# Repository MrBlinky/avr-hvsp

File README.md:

# avr-hvsp
High voltage serial programmer for AVR Attiny devices

* Easy to make programmer using 12V DC-DC converter with enable and ATMEGA32U4 Beetle board.
* Programs AVR Attiny devices in high voltage mode to recover fuse settings and allow reset pin to be used as GPIO pin.
* Works with Arduino IDE / AVRdude.
* No hassle with Windows driver utilities. Uses built in windows 10 driver or Arduino IDE driver.

## Parts

|Qty. | Discription                                                    |
| --- | -------------------------------------------------------------- |
| 1   | 12V DC-DC converter/booster module with enable                 |
| 1   | ATMEGA32U4 Beetle board without parts on PCB bottom + headers (No 3.3V pin and no extra GND pins on top row.) |
| 1   | 3 mm Red LED                                                   |
| 1   | 3 mm Yellow LED                                                |
| 1   | 3 mm Green LED                                                 |
| 5   | 470 Ohm resistor  (1/8 Watt)                                   |
| 2   | 1K resistor (1/8 Watt)                                         |
| 1   | PM48XP P-channel MOSFET SOT23 package (optional)*              |
| 1   | 8 pin header (for programming connector)                       |
| 1   | 2 pin header (for DC-DC converter)                             |
| 3   | 1 pin header (for DC-DC converter)                             |
| 1   | 8 pin IC socket                                                |
| 1   | 6x6mm tactile button                                           |
 
*A MOSFET is recommended for a more powerful VCC. However if devices are
 only programmed using the IC socket or in low power circuits (<20mA),
 the MOSFET can be left out. In that case VCC is powered by a GPIO pin
 by shorting jumper J1. When using a MOSFET, Jumper J1 must be left open.

Revision 1.1 PCB can be ordered through [OSH Park](https://oshpark.com/shared_projects/vXxMrB8z)

## Assembly

Assemble parts with low height first (programming header, MOSFET at bottom, resistors IC socket, button, LEDs and modules as last).
Check a parts aligment after soldering the first pin and when it's aligned properly solder remaining pins.

Before soldering the module headers, place headers with long end into main PCB and mount modules on top for easy aligment. Solder one pin of each header at top of module and check if headers are straight then solder remaining pins at top of the modules. Cut excess length of header pins at bottom of the main PCB and then solder them.

## upload programmer firmware

* Open **hvsp.ino** sketch by double clicking or open file with Arduino IDE
* Select **Arduino Leonardo** board from **Tools** menu.
* Select **port** from **Tools** menu.
* Upload sketch

## Programming a device

Insert 8-pin DIP devices in to socket or wire-up device to programming header (check device datasheet for wiring).
Upload a sketch using Arduino IDE or upload a hex file directly using AVRdude.

LED status:
* Red LED on: 12V VPP programming voltage on. Red LED off: Programming voltage off.
* Yellow LED on: 5V VCC on. Yellow LED off: 5V VCC off.
* Green LED on: Both programming and VCC are off. Green LED off: VPP and/or VCC on.

Button control:

Short press (< 500 ms): Toggle VCC on/off.
long press (>= 500 ms): TO DO

### using Arduino IDE

select **Arduino as ISP (ATmega32U4)** as **programmer** from **Tools** menu

### using AVRdude

Use **-carduino** as programmer switch and specify serial port with *-P* switch

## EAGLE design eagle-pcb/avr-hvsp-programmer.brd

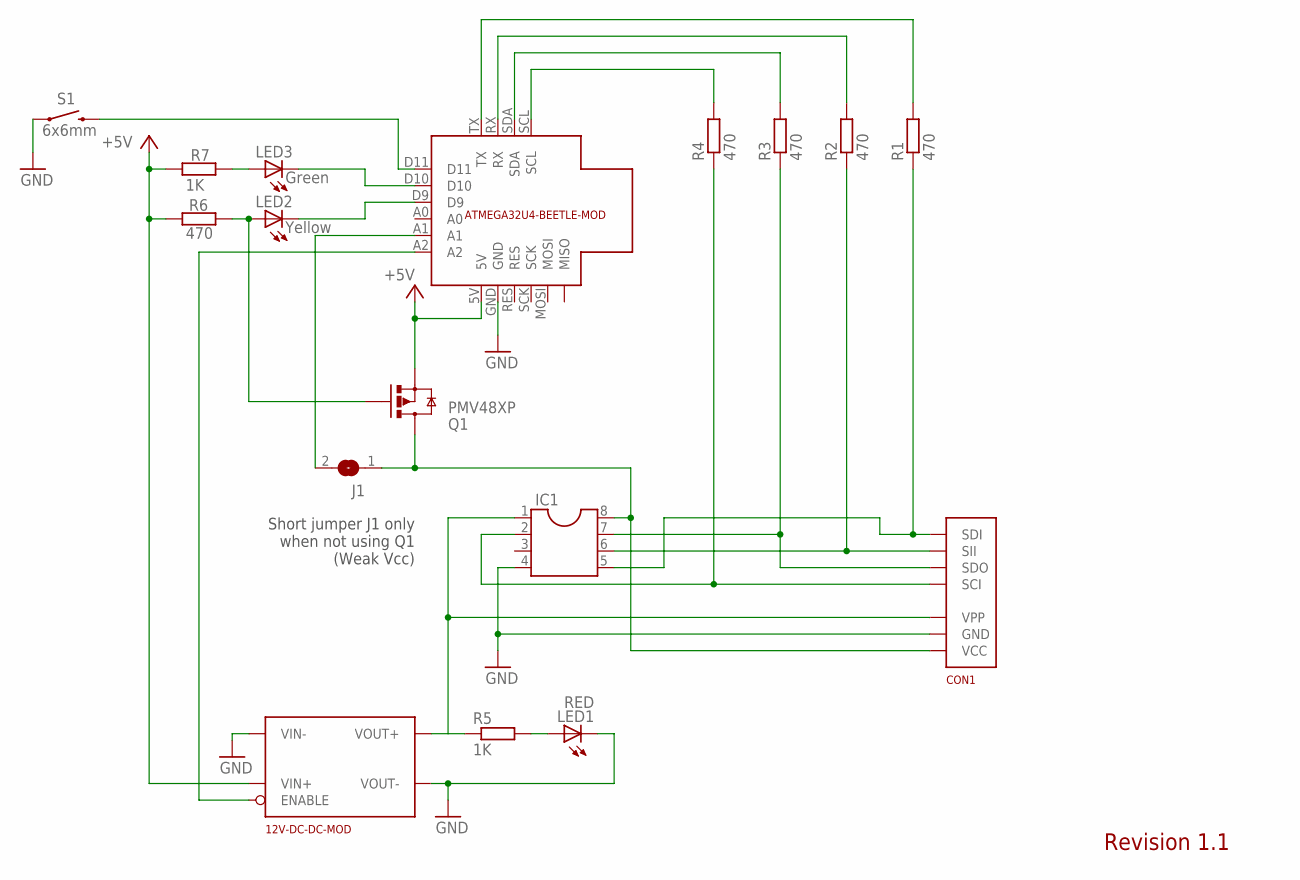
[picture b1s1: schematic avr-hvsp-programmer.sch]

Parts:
12V-DC-DC-MOD: 12V-DC-DC-CONVERTER-WITH_ENABLE; 12V-DC-DC-CONVERTER-WITH-ENABLE
ATMEGA32U4-BEETLE-MOD: ATMEGA32U4-BEETLE-BOARD
CON1: HVSP-HEADER
IC1: DIL8S; SOCKET-08
J1: SJ
LED1: RED; LED3MM
LED2: Yellow; LED3MM
LED3: Green; LED3MM
Q1: PMV48XP; SOT23-3
R1, R2, R3, R4: 470; 0207/7
R5, R7: 1K; 0207/10
R6: 470; 0207/10
S1: 6x6mm; TACTILE_SWITCH_PTH_6.0MM

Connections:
+5V: 12V-DC-DC-MOD.VIN+, ATMEGA32U4-BEETLE-MOD.5V, Q1.2 (S), R6.1, R7.1
GND: 12V-DC-DC-MOD.VIN-, 12V-DC-DC-MOD.VOUT-, ATMEGA32U4-BEETLE-MOD.GND, CON1.GND, IC1.4, LED1.K (C), S1.1
LED2: ATMEGA32U4-BEETLE-MOD.D9, LED2.K (C)
LED3: ATMEGA32U4-BEETLE-MOD.D10, LED3.K (C)
unnamed: ATMEGA32U4-BEETLE-MOD.TX, R1.2
unnamed: ATMEGA32U4-BEETLE-MOD.RX, R2.2
unnamed: ATMEGA32U4-BEETLE-MOD.SDA, R3.2
unnamed: ATMEGA32U4-BEETLE-MOD.SCL, R4.2
R-LED1: LED1.A, R5.2
R-LED2: LED2.A, Q1.1 (G), R6.2
R-LED3: LED3.A, R7.2
S1: ATMEGA32U4-BEETLE-MOD.D11, S1.3 (2)
SCI: CON1.SCI, IC1.2, R4.1
SDI: CON1.SDI, IC1.5, R1.1
SDO: CON1.SDO, IC1.7, R3.1
SII: CON1.SII, IC1.6, R2.1
VCC: CON1.VCC, IC1.8, J1.1, Q1.3 (D)
VCC_WEAK: ATMEGA32U4-BEETLE-MOD.A1, J1.2
VPP: 12V-DC-DC-MOD.VOUT+, CON1.VPP, IC1.1, R5.1
VPP_ENABLE: 12V-DC-DC-MOD.ENABLE, ATMEGA32U4-BEETLE-MOD.A2

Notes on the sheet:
Short jumper J1 only when not using Q1 (Weak Vcc)
Revision 1.1

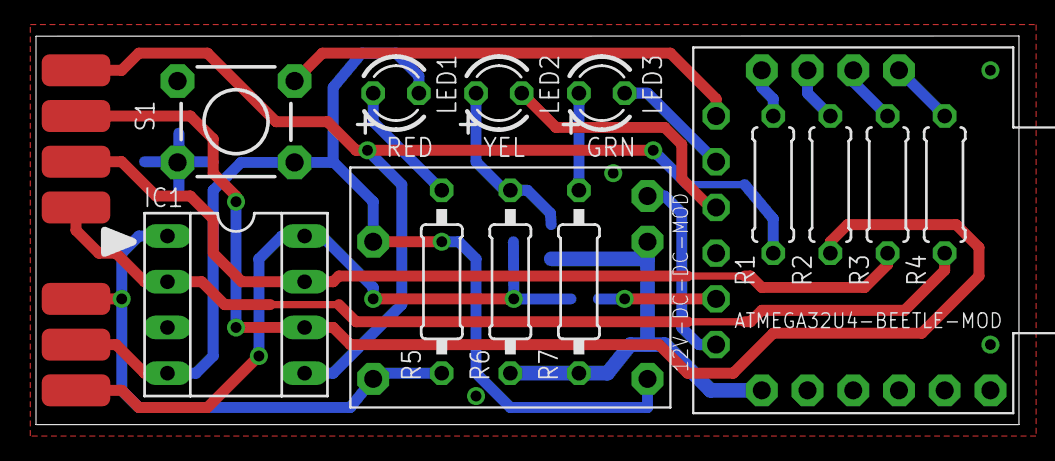
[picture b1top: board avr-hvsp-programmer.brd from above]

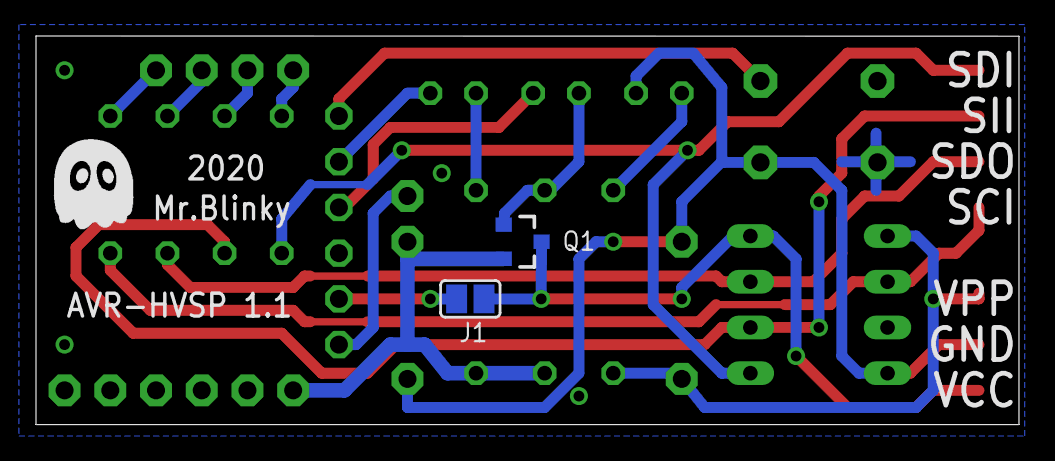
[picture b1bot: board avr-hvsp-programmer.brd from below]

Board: 2 copper layers, 54.6 x 21.6 mm, 17 parts (2 on the bottom side), 20 nets.

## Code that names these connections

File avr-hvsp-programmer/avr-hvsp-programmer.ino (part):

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
// pin configurations (Using direct IO instead of slow DigitalRead/Write and pinMode)

#define HVSP_SCI_BIT    0       // 3/SCL output connected to SCI pin
#define HVSP_SCI_PIN    PIND
#define HVSP_SCI_PORT   PORTD
#define HVSP_SCI_DDR    DDRD

#define HVSP_SDO_BIT    1       // 2/SDA input/output connected to Serial Data Output (SDO) pin
#define HVSP_SDO_PIN    PIND
#define HVSP_SDO_PORT   PORTD
#define HVSP_SDO_DDR    DDRD

#define HVSP_SII_BIT    2       // RX output connect to Serial Instruction Input (SII) pin
#define HVSP_SII_PIN    PIND
#define HVSP_SII_PORT   PORTD
#define HVSP_SII_DDR    DDRD

#define HVSP_SDI_BIT    3       // TX output connected to Serial Data Input (SDI) pin
#define HVSP_SDI_PIN    PIND
#define HVSP_SDI_PORT   PORTD
#define HVSP_SDI_DDR    DDRD
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#define BUTTON_DDR      DDRB

#define GREEN_LED_BIT   6       // D10 active low turns LED on. 
#define GREEN_LED_PIN   PINB    // Status LED to tell both VCC and VPP are disabled
#define GREEN_LED_PORT  PORTB
#define GREEN_LED_DDR   DDRB

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#define VCC_DDR         DDRF

#define VPP_BIT         5       // A2 active low turns the 12V DC-DC converter on. 
#define VPP_PIN         PINF    // The RED VPP LED is powered by 12V
#define VPP_PORT        PORTF
#define VPP_DDR         DDRF

#define BUILTIN_LED_BIT  7       // D13 Leonardo/Beetle board built in LED  
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#define VCC_LED_ON      (VCC_LED_PORT    &= ~(1 << VCC_LED_BIT))
#define VCC_OFF         (VCC_PORT        &= ~(1 << VCC_BIT))
#define VCC_ON          (VCC_PORT        |=  (1 << VCC_BIT))
#define VPP_OFF         (VPP_PORT &= ~(1 << VPP_BIT))
#define VPP_ON          (VPP_PORT |= (1 << VPP_BIT))

#define BUILTIN_LED_OFF (BUILTIN_LED_PORT  &= ~(1 << BUILTIN_LED_BIT))
#define BUILTIN_LED_ON  (BUILTIN_LED_PORT  |=  (1 << BUILTIN_LED_BIT))
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
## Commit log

2020-04-12 add Eagle files
2020-04-12 added source and binary

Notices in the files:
avr-hvsp-programmer/avr-hvsp-programmer.ino:
AVR High Voltage Serial Programmer 1.01 by Mr.Blinky Mar-Apr.2020 CC0 Licence
parts and their libraries:
SparkFun-Switches: Licensing: Creative Commons ShareAlike 4.0 International - https://creativecommons.org/licenses/by-sa/4.0
